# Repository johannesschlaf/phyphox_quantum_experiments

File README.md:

# Quantum experiments with phyphox
Language: **English** | [Deutsch](./README.de.md)

In this repository there are all the files needed for the ready-made phyphox-based quantum experiments.
 - **English instructions regarding the conduction of the experiments are now ready and available.**
 - **English instructions regarding the manufacturing of the DIY setup for measuring Planck's constant are currently in the works. They will be available in the future.**

## Measuring Planck's constant
In this experiment, the threshold voltages of LEDs with different peak wavelengths $\lambda$ are measured. From these, the respective photon energy can be calculated and plotted over $\nu=\frac{c}{\lambda}$. Planck's constant equals the slope of the line of best fit through these data pairs.<br>
This experiments needs a DIY setup that needs to be manufactured. Important manufacturing techniques include 3D printing, through-hole soldering of electronic components on a board, as well as sealing-in threaded inserts. In the folder _Instructions_ you will find a detailed construction manual.

## BB84 analogy
The BB84 protocol is a procedure used in quantum cryptography, in which single photons in specific polarisation states are sent and measured in a specific way in order to securely generate and transmit keys simultaneously. Further information can be found in the guide in the folder _Instructions_.<br>
The basic experiment requires just two smartphones, the simulation fo an eavesdropping attempt requires three smartphones.

## Quantized conductance
...coming soon...

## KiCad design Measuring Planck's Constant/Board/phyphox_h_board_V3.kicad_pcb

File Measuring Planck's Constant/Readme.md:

# Measuring Planck's Constant
Language: **English** | [Deutsch](./README.de.md)

In this experiment, the threshold voltages of LEDs with different peak wavelengths $\lambda$ are measured. From these, the respective photon energy can be calculated and plotted over $\nu=\frac{c}{\lambda}$. Planck's constant equals the slope of the line of best fit through these data pairs.<br>
This experiment needs a DIY setup that needs to be manufactured. Important manufacturing techniques include 3D printing, through-hole soldering of electronic components on a board, as well as sealing-in threaded inserts. In the folder _Instructions_ you will find a detailed construction manual.

<br><br>
<i>
Thanks to:
- Pierre Kellermann for designing a prototype for the blackout box as well as the stabilisation aid.
- Marius Rieck for creating and testing a DIY workshop concept for pupils and providing the respective presentation slides.
</i>

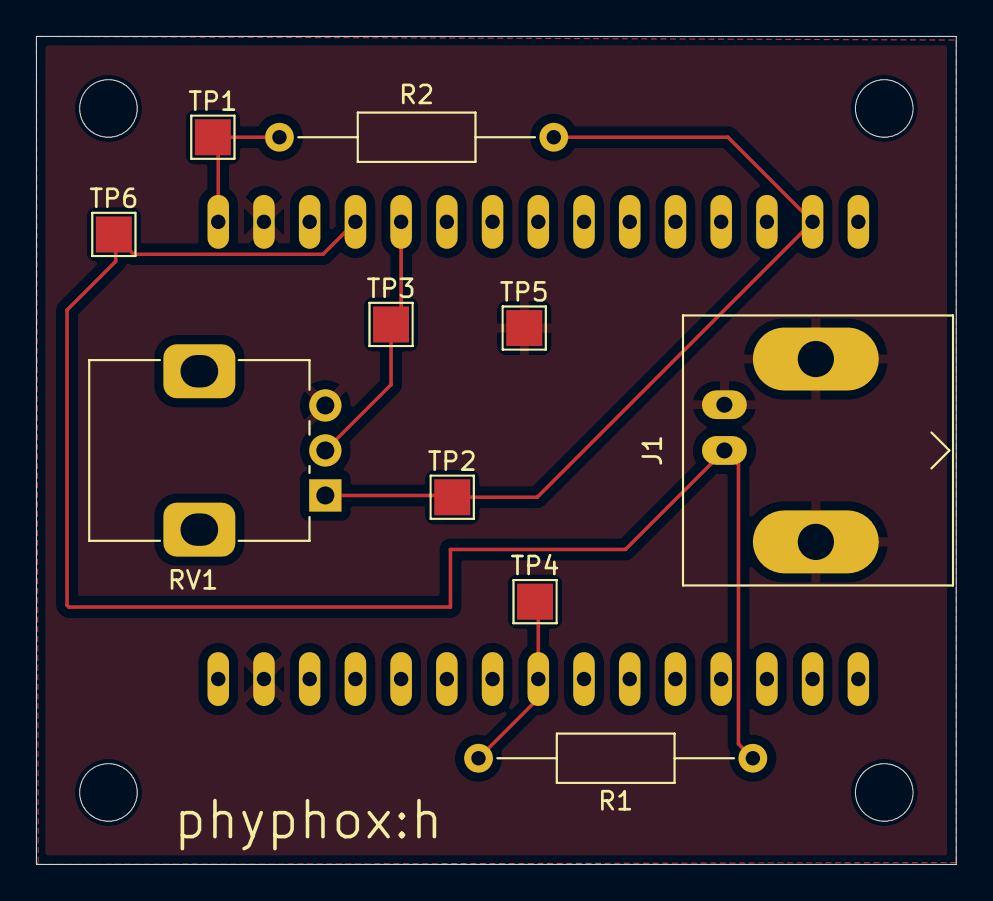
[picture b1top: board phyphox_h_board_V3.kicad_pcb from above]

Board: 2 copper layers, 51.1 x 46.0 mm, 15 parts (1 on the bottom side), 6 nets.

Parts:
H1, H2, H3, H4: MountingHole; MountingHole_3.2mm_M3
J1: Conn_Coaxial_Small; BNC_Amphenol_B6252HB-NPP3G-50_Horizontal
R1, R2: 100R; R_Axial_DIN0207_L6.3mm_D2.5mm_P15.24mm_Horizontal
RV1: R_Potentiometer; Potentiometer_Alps_RK09K_Single_Vertical
TP1, TP2, TP3, TP4, TP5, TP6: TestPoint; TestPoint_Pad_2.0x2.0mm
U1: NodeMCU ESP32; NodeMCU-ESP32

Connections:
GND: J1.2 (Ext), RV1.3, TP5.1, U1.2 (GND), U1.29 (GND)
unnamed: J1.1 (In), R1.1, TP6.1, U1.4 (D2)
unnamed: R2.1, TP1.1, U1.1 (3,3V)
unnamed: RV1.2, TP3.1, U1.5 (D4)
unnamed: R2.2, RV1.1, TP2.1, U1.14 (D22)
unnamed: R1.2, TP4.1, U1.23 (D25)

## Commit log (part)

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2026-05-12 Add files via upload
    Arduino Code for the phyphox:h box
2026-05-27 Update README.md
    Added German description of the experiments
2026-05-27 Rename Readme.de.md to README.de.md
2026-05-27 Update README.md
    Added English Readme
2026-05-27 Update README.de.md
    Formulierung bei BB84 berichtigt.
2026-05-27 Update README.md
    Removes German heading
2026-05-27 Update README.md
    Link zur deutschen Readme
2026-05-27 Update README.md
    Added formatting
2026-05-27 Update README.de.md
    Formatierung und Link zur englischen Readme hinzugefügt.
2026-05-27 Update README.de.md
    Formel ergänzt
2026-05-27 Update README.md
    Added to formula
2026-05-27 Add files via upload
    Handreichung und Auswertungsbogen zu BB84 hochgeladen
2026-05-27 Add files via upload
    Anleitungen für SuS und Studierende hochgeladen
2026-05-27 Add files via upload
    Handreichung für Lehrkräfte hochgeladen.
2026-05-28 Add files via upload
    Experimente zu BB84 hochgeladen
2026-05-28 Add files via upload
    Hinzufügen aufschlussreicher benannter Experimente
2026-05-28 Add files via upload
    Hinzufügen der Experimente in Form einer ZIP-Datei zum Download
2026-05-28 Rename 2026_03_19_QC-Bundle_V4.1.zip to 00_2026_03_19_QC-Bundle_V4.1.zip
    Umbenennen des ZIP-files
2026-05-28 Add files via upload
    QR-Code in Handreichung aktualisiert
2026-05-28 Add files via upload
    Abbildungen zur BB84-Handreichung hochgeladen.
2026-05-28 Add files via upload
    Typst-Dateien zu BB84 hochgeladen
2026-05-28 Rename Test3.typ to Handreichung BB84.typ
2026-05-28 Rename Test4.typ to Auswertungsbogen BB84.typ
2026-05-28 Rename Measuring Planck's Constant/Instructions/Anleitung Studierende.pdf to Measuring Planck's Constant/Instructions/de/Anleitung Studierende.pdf
2026-05-28 Rename Measuring Planck's Constant/Instructions/Anleitung SuS.pdf to Measuring Planck's Constant/Instructions/de/Anleitung SuS.pdf
2026-05-28 Rename Measuring Planck's Constant/Instructions/Handreichung Lehrkräfte.pdf to Measuring Planck's Constant/Instructions/de/Handreichung Lehrkräfte.pdf
2026-05-28 Rename BB84 Analogy/Instructions/Auswertungsbogen BB84.pdf to BB84 Analogy/Instructions/de/Auswertungsbogen BB84.pdf
2026-05-28 Rename BB84 Analogy/Instructions/Handreichung BB84.pdf to BB84 Analogy/Instructions/de/Handreichung BB84.pdf
2026-05-28 Rename Test.typ to Versuchsanleitung.typ
2026-05-28 Rename Test10.typ to Handreichung Lehrkräfte.typ
2026-05-28 Rename Anleitung Studierende.pdf to Versuchsanleitung Studierende.pdf
2026-05-28 Rename Anleitung SuS.pdf to Versuchsanleitung SuS.pdf
2026-05-28 Rename phyphox_d_Einlage_V3.1E.stp to phyphox_LED_Reflection_Insert_V3.1E.stp
2026-05-28 Rename phyphox_d_LED-Einsatz_V3.3_noname.stp to phyphox_LED_inset_V3.3.stp
2026-05-28 Rename phyphox_d_oben_V3.5.4.stp to phyphox_LED_Top_V3.5.4.stp
2026-05-28 Rename phyphox_LED_inset_V3.3.stp to phyphox_LED_Inset_V3.3.stp
2026-05-28 Rename phyphox_d_unten_V3.5.3.stp to phyphox_LED_Bottom_V3.5.3.stp
2026-05-28 Rename phyphox_h_Deckel_V4.2.1.stp to phyphox_h_Top_V4.2.1.stp
2026-05-28 Rename phyphox_h_Unterseite_V4.2.3_noname.stp to phyphox_h_Bottom_V4.2.3.stp
2026-05-28 Rename phyphox_h_UpperLayer_V4.2.stp to phyphox_h_Scale_V4.2.stp
2026-05-28 Rename Hocker Ledkasten v1.stl to Stabilisation_Aid_PBK.stl
2026-05-28 Rename Photoeffekt_V3.kicad_pcb to phyphox_h_board_V3.kicad_pcb
2026-05-28 Update PHOV4.1.ino
    English comments
2026-05-28 Rename Handreichung Lehrkräfte.pdf to Handreichung für Lehrkräfte.pdf
2026-05-28 Rename Handreichung Lehrkräfte.typ to Handreichung für Lehrkräfte.typ
2026-05-28 Add files via upload
    Bauanleitung hinzugefügt
2026-05-28 Rename Test5.typ to Handreichung zur Fertigung des Aufbaus.typ
2026-05-28 move folder
2026-05-28 Vers
2026-05-28 Rename phyphox_LED_Reflection_Insert_V3.1E.stp to phyphox_LED_Reflective_Insert_V3.1E.stp
2026-06-02 Add files via upload
    Beschädigte PDFs austauschen
